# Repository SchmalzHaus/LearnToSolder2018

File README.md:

# LearnToSolder2018

## Introduction

For the past couple years, Deanna Schmalz has designed a simple circuit board which we then use to teach learn to solder classes. We  make enough boards and buy enough parts to teach all of the 4th graders at Glen Lake Elementary School in Minnetonka Minnesota, USA how to solder.

This site contains all of the information related to this year's Learn To Solder board. If you want to learn more about how to solder, if you want to know what you need to purchase so you can solder at home, or if you want to make more of these boards for yourself or your organization, this site has everything you'll need.

If you want to reach Brian Schmalz (brian@schmalzaus.com) or Deanna (deanna@schmalzhaus.com) to ask us any questions, please do so. 

All text files and designs on this site are Open Source. You are free to use these files and do whatever you wish with them.

## LearnToSolder 2018 Kit Contents

* Qty 1 Circuit Board - with pre-programmed PIC12F1572 CPU soldered on
* Qty 2 Switches
* Qty 2 Switch caps (various colors)
* Qty 2 Red LEDs
* Qty 2 Green LEDs
* Qty 2 Yellow LEDs
* Qty 2 Blue LEDs
* Qty 1 CR2032 Battery Holder
* Qty 1 CR2032 Battery
* Qty 2 random value through hole resistors (for Octopus eyebrows)

## Tools

To solder electronic kits together, you will need (at a minimum)

### Soldering Iron

We do not recommend buying a soldering iron unless it is 'temperature controlled'. This means you get to set the tip temperature with a knob or buttons, and the iron will only heat up as much as it needs to in order to maintain that temperature. Using a non-temp controlled iron has, in our experience, led to lots of frustration and failed kits.

This is the iron we recommend, as we've had great experience with it and it is very inexpensive : [http://www.hobbyking.com/hobbyking/store/__19240__Soldering_Station_with_Adjustable_Heat_Range_US_Warehouse_.html]

You can also by this same type of iron from many other places, including Amazon and Ebay, but the price tends to be a bit higher. Some of the companies listed below under Other Soldering Kits also sell tools like irons.

### Solder

For beginners, we strongly recommend using leaded solder (rather than lead-free). The safety risk is very minimal (just be sure to wash your hands with soap when you are done) and it is far, far easier to get good soldered joints with leaded solder when you're just starting to learn soldering. You can buy leaded electronic solder at many on-line stores like SparkFun [https://www.sparkfun.com/products/9161] or Adafruit [https://www.adafruit.com/products/1886]. Make sure to buy 60/40 or 63/37 (those numbers represent the ratio of tin to lead in the solder) electronic solder - there are other solders out there (like silver solder for jewelry for example) that won't work for electronics.

### Brass Sponge

When you buy your iron, buy a bras sponge if the iron doesn't already come with it. These are much better than the watter sponge that comes with the iron for cleaning the tip of the soldering iron.

### Wire Cutter

All of the companies listed below sell small wire cutters, or you can get them locally at hardware stores too. The best kind is something that will allow you to cut off wires flush with the board - sometimes called 'flush cutters'. For example [https://www.sparkfun.com/products/11952] or [https://www.adafruit.com/products/152]

### Other tools

There are lots of other tools you can get to help you while solder. Third-hands can be very useful. Needle nose pliers, solder suckers, magnifying glasses, solder wick, wire strippers, etc.

## Kit Assembly Process (overview)

There are only a couple steps to assembling this kit, as it is very simple. If you have done soldering before, you can just walk through this overview of the steps to complete your kit. If you want to learn more about how to do the actual soldering of a joint, the following websites and resources will give you plenty of background materials and explanations:

https://learn.sparkfun.com/tutorials/how-to-solder---through-hole-soldering

http://www.howtogeek.com/63630/how-to-use-a-soldering-iron-a-beginners-guide/

https://cdn-learn.adafruit.com/downloads/pdf/adafruit-guide-excellent-soldering.pdf

### Steps:

1. Solder the eight LEDs. Follow the color guide on the circuit board. Long lead (wire) goes into square hole. You sometimes have to wiggle the LEDs a bit to get them to press all the way flat down on the top side of the board due to a thick spot on the LED leads. Bend the leads apart on the back side to keep the LEDs in place as you solder the LED wires on the back side of the board. Clip the excess leads on the back of the board once soldered.

2. Insert the two switches into the board. Make sure all parts go into the board from the top side (with the thick white lines) to the back side. The switches snap down into the board - you sometimes have to press them in hard to get them to snap. But be careful - sometimes the pins come somewhat bent and pressing them down hard will bend them further if all four are not in the holes as you press down. Solder the four pins of each switch on the back side of the board. Snap the two switch caps down on the switches.

3. Insert the battery holder to the front of the board, being careful to align the outline of the battery hold to the white outline on the top of the board (there is a square tab on the battery holder than needs to match up to the square tab part of the outline). While holding the battery holder into the board, flip it over and solder both pins.

4. Insert the two eyebrow resistors. They are not part of the circut but are just for looks. Bend each lead of the reisstor so that the leads go through the board and the resistor sits flush on the board. Solder the leads on the back side of the board and clip excess lead length.

4. Insert the battery into the holder, flat shiny + side up. Press the buttons to see your LEDs light. If you hold down a button, the octopus will display a pattern.

## Other Soldering Kits

There are SO MANY kits available today, it's impossible to list all of them, or even the good ones. If you do a Google search for "electronic soldering kit" you will find lots of them out there. Some are easier than others, and some come with great instructions (and some don't).

We buy a lot of high quality soldering kits from the following on-line companies:

Evil Mad Scientist [http://shop.evilmadscientist.com/]
* Their Boldport Buggy is excellent [http://shop.evilmadscientist.com/]
* The Flickery Flame is a great beginner kit [http://shop.evilmadscientist.com/productsmenu/793]

Spark Fun Electronics [https://www.sparkfun.com/]
* They have a whole catagory of 'kits', some of which are soldering kits [https://www.sparkfun.com/categories/157]
* The SparkFun Simon Says - Through-Hole kit is really fun [https://www.sparkfun.com/products/10547]

Adafruit [https://www.adafruit.com/]
* The Drawdio is quite fun [https://www.adafruit.com/categories/28]
* Their Minty Boost is actually quite useful [https://www.adafruit.com/products/14]

SeeedStudio [http://www.seeedstudio.com/]
* Their 4-Soldering Zoo Kit looks super cute [https://www.seeedstudio.com/item_detail.html?p_id=1950]

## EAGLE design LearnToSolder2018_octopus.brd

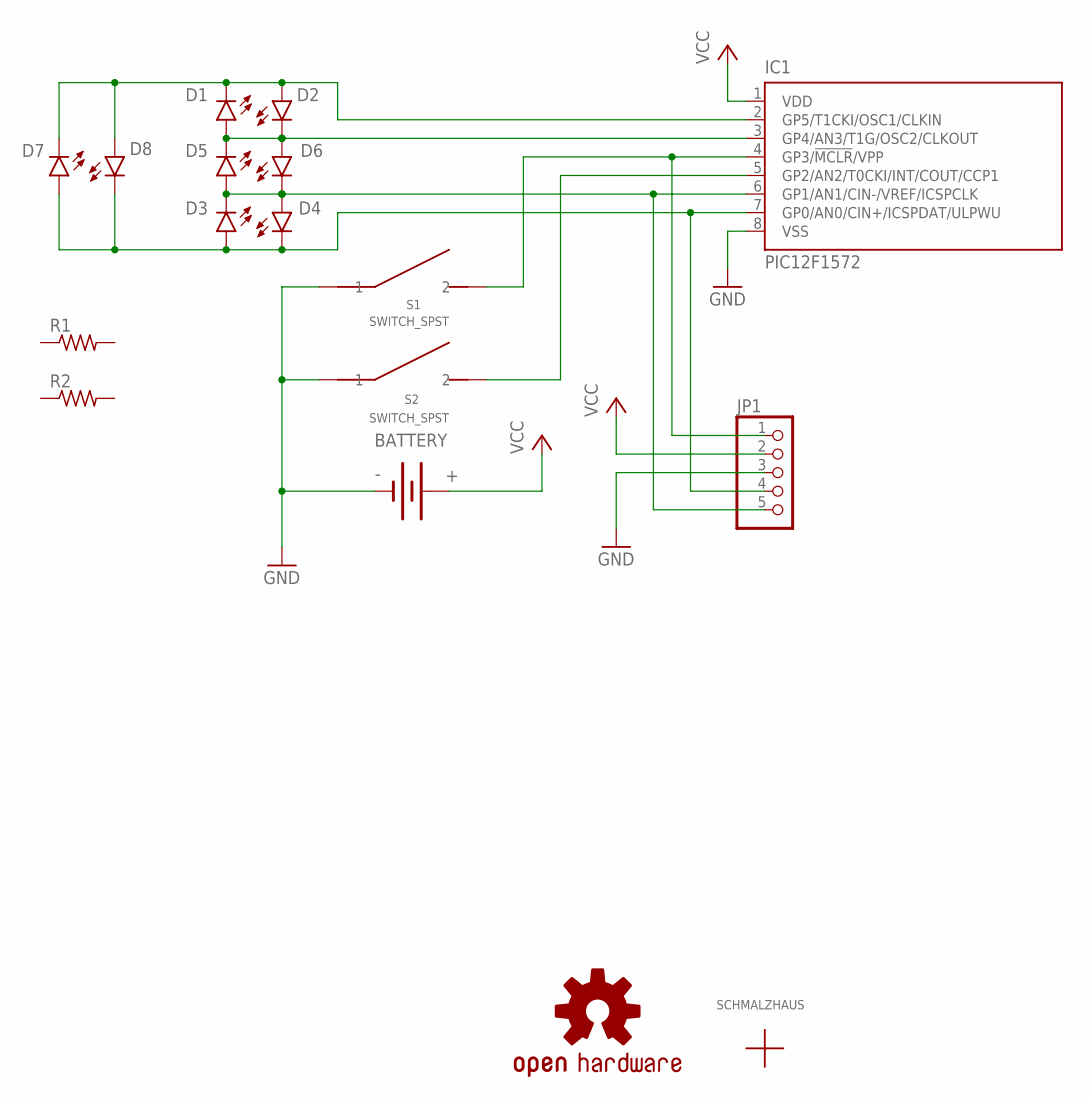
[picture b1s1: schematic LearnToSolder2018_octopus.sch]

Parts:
BATTERY: BATTERY20PTH; BATTCOM_20MM_PTH
D1, D2, D3, D4, D5, D6, D7, D8: LED5MM
IC1: PIC12F1572; SO-08
JP1: PINHD-1X5; 1X05
LOGO1: OSHW-LOGOMINI; OSHW-LOGO-MINI
R1, R2: R-US_0309/12; 0309/12
S1, S2: SWITCH_SPST; OMRON-12MMX12MM_SPST-B3F-4000
U$3: SCHMALZHAUSSCHMALZHAUS_SMALL; SCHMALZHAUS_SMALL

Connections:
GND: BATTERY.2 (-), IC1.8 (VSS), JP1.3, S1.1, S1.2 (1), S2.1, S2.2 (1)
unnamed: IC1.4 (GP3/!MCLR!/VPP), JP1.1, S1.3 (2), S1.4 (2)
unnamed: IC1.5 (GP2/AN2/T0CKI/INT/COUT/CCP1), S2.3 (2), S2.4 (2)
unnamed: D3.A, D4.K (C), D7.A, D8.K (C), IC1.7 (GP0/AN0/CIN+/ICSPDAT/ULPWU), JP1.4
unnamed: D3.K (C), D4.A, D5.A, D6.K (C), IC1.6 (GP1/AN1/CIN-/VREF/ICSPCLK), JP1.5
unnamed: D1.K (C), D2.A, D7.K (C), D8.A, IC1.2 (GP5/T1CKI/OSC1/CLKIN)
unnamed: D1.A, D2.K (C), D5.K (C), D6.A, IC1.3 (GP4/AN3/T1G/OSC2/CLKOUT)
VCC: BATTERY.1 (+), IC1.1 (VDD), JP1.2

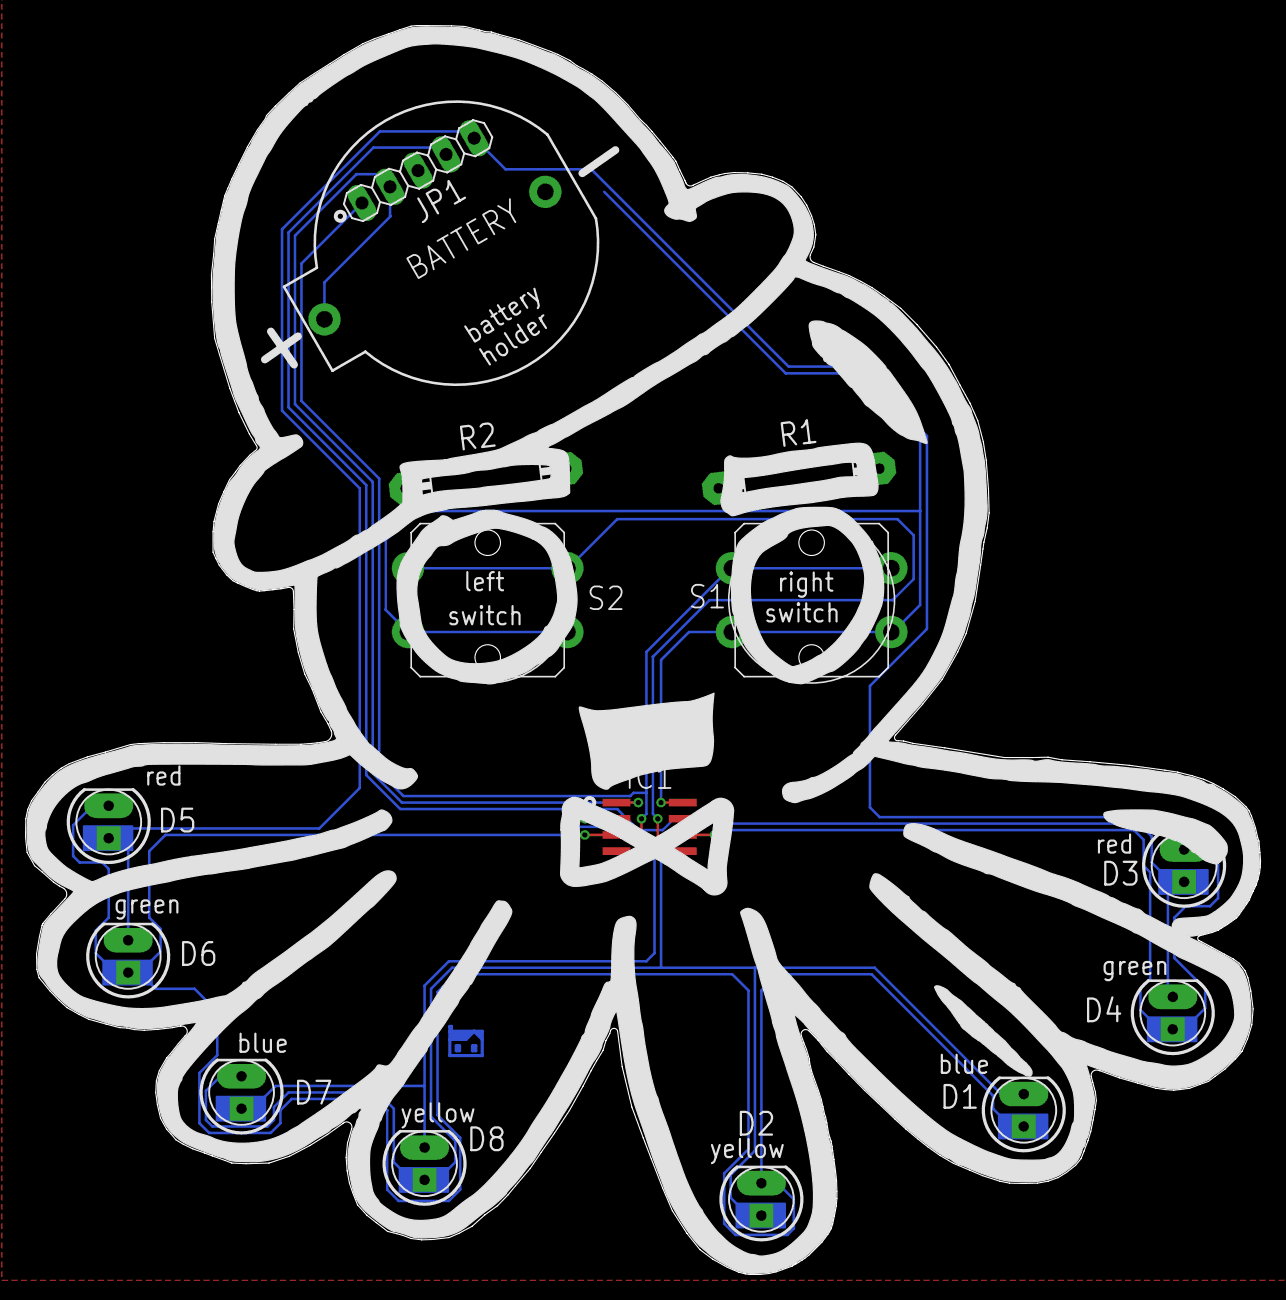
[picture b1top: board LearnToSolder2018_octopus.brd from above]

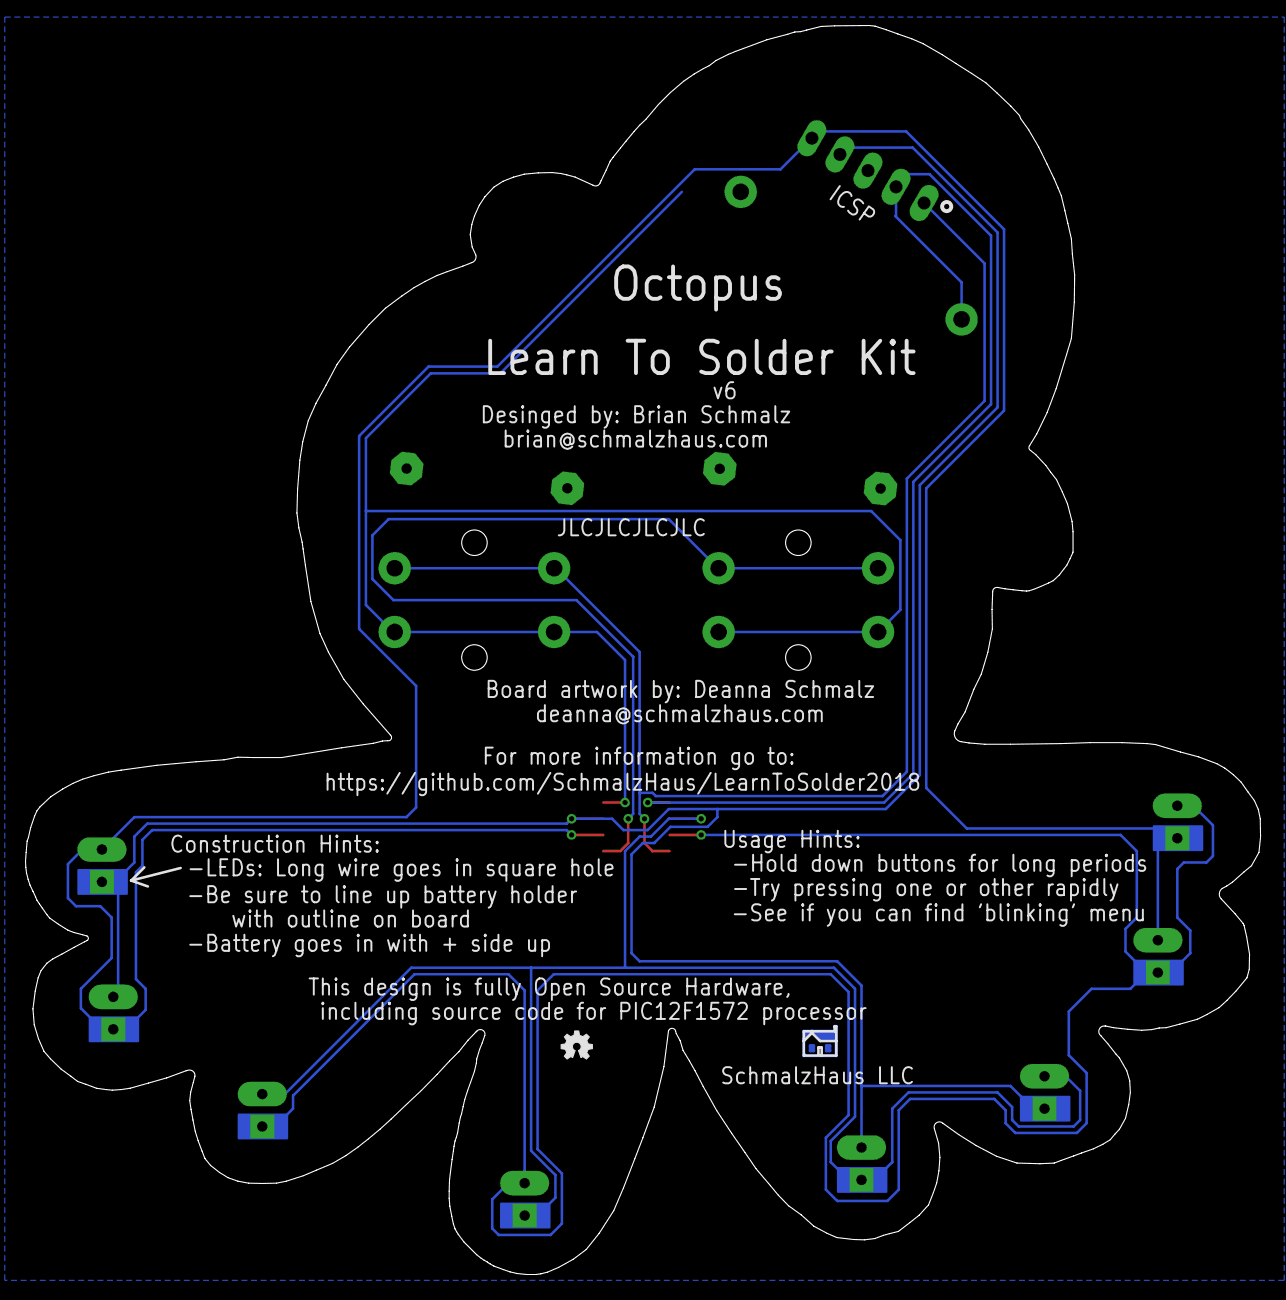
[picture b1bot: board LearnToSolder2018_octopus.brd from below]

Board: 2 copper layers, 96.9 x 97.9 mm, 17 parts (2 on the bottom side), 8 nets.

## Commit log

2018-03-20 Starting to get code working on breadboard prototype.
2018-03-22 Prototype board layout (just circuit, no board outline or artwork yet)
2018-04-04 Leakage through LEDs from +3 to GND too much chance for battery draining/light up. Redesigned to use Charlieplexing. Re layed out board to be a bit more aesthetic. Added some extra practice resistors.
2018-04-11 v0.1 firmware - first test with Charliplexed boards - simple light sequence works!
2018-04-11 v0.2 - fixed LED output states when off to reduce sleep current.
2018-04-15 Software v0.3 : true charliplexing code, arbitrary LEDs on/off now, effects are state machine based with independent soft timers.
2018-04-20 v4 of board done and sent out for prototype fab.
2018-04-26 v5 of Octopus board sent to fab. Updated based on feedback from v4 : * Made outline not have sharp internal cuts - rounded them over * Made all pads that will be soldered on back of board much larger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
2018-05-05 Minor playing with 'two at a time' Charliplexing to improve LED brightness and minimize differences between boards in brightness.
2018-05-10 WIP: Starting to get multiple pattern state machines working
2018-05-11 Patterns now all array based.
2018-05-17 Got tmr0 dialed in to cycle through all 8 LEDs in exactly 1 ms. Added system wake timer to go to sleep after x minutes of running
2018-05-22 Added switch debouncing
2018-05-22 Got final 'primary' pattern working for left and right buttons.
2018-05-23 Version 1.0 : got all major features working except for 'menu'. Final code used for Learn To Solder class.
2022-12-04 Adding instruction sheet, removing incorrect pictures.
2022-12-04 Added images, updated readme.md to be accurate for this kit.
2022-12-04 Fixed image link in readme.md.

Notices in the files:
parts and their libraries:
SparkFun-Aesthetics: Licensing: Creative Commons ShareAlike 4.0 International - https://creativecommons.org/licenses/by-sa/4.0
